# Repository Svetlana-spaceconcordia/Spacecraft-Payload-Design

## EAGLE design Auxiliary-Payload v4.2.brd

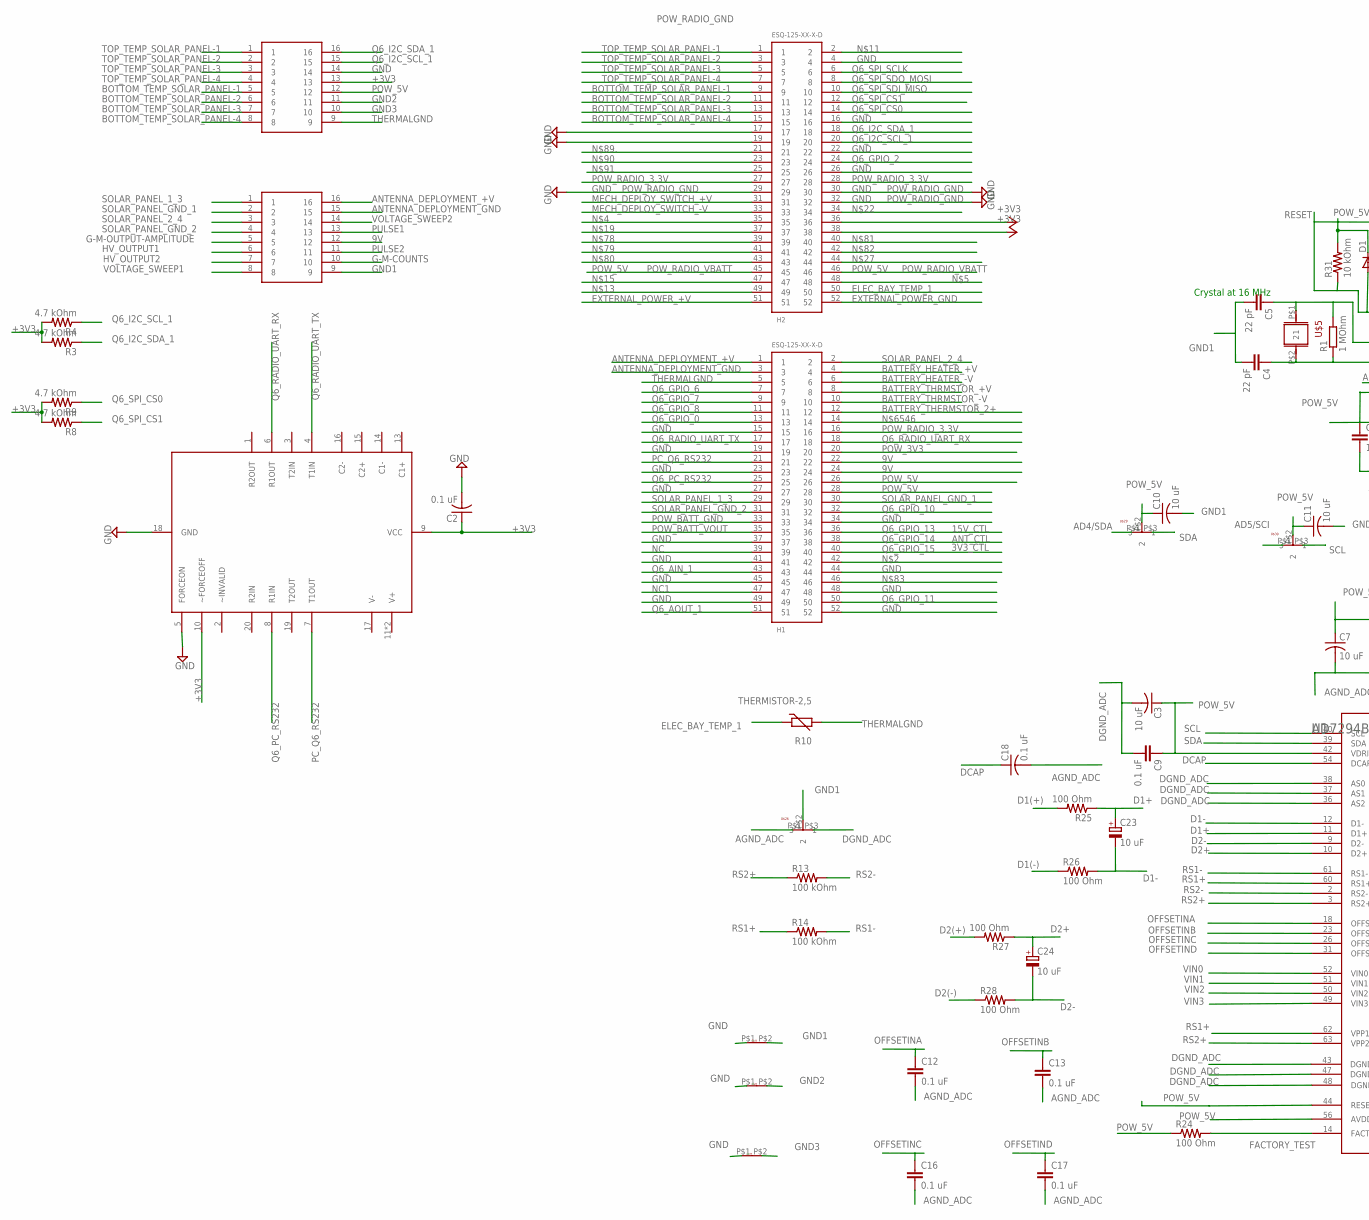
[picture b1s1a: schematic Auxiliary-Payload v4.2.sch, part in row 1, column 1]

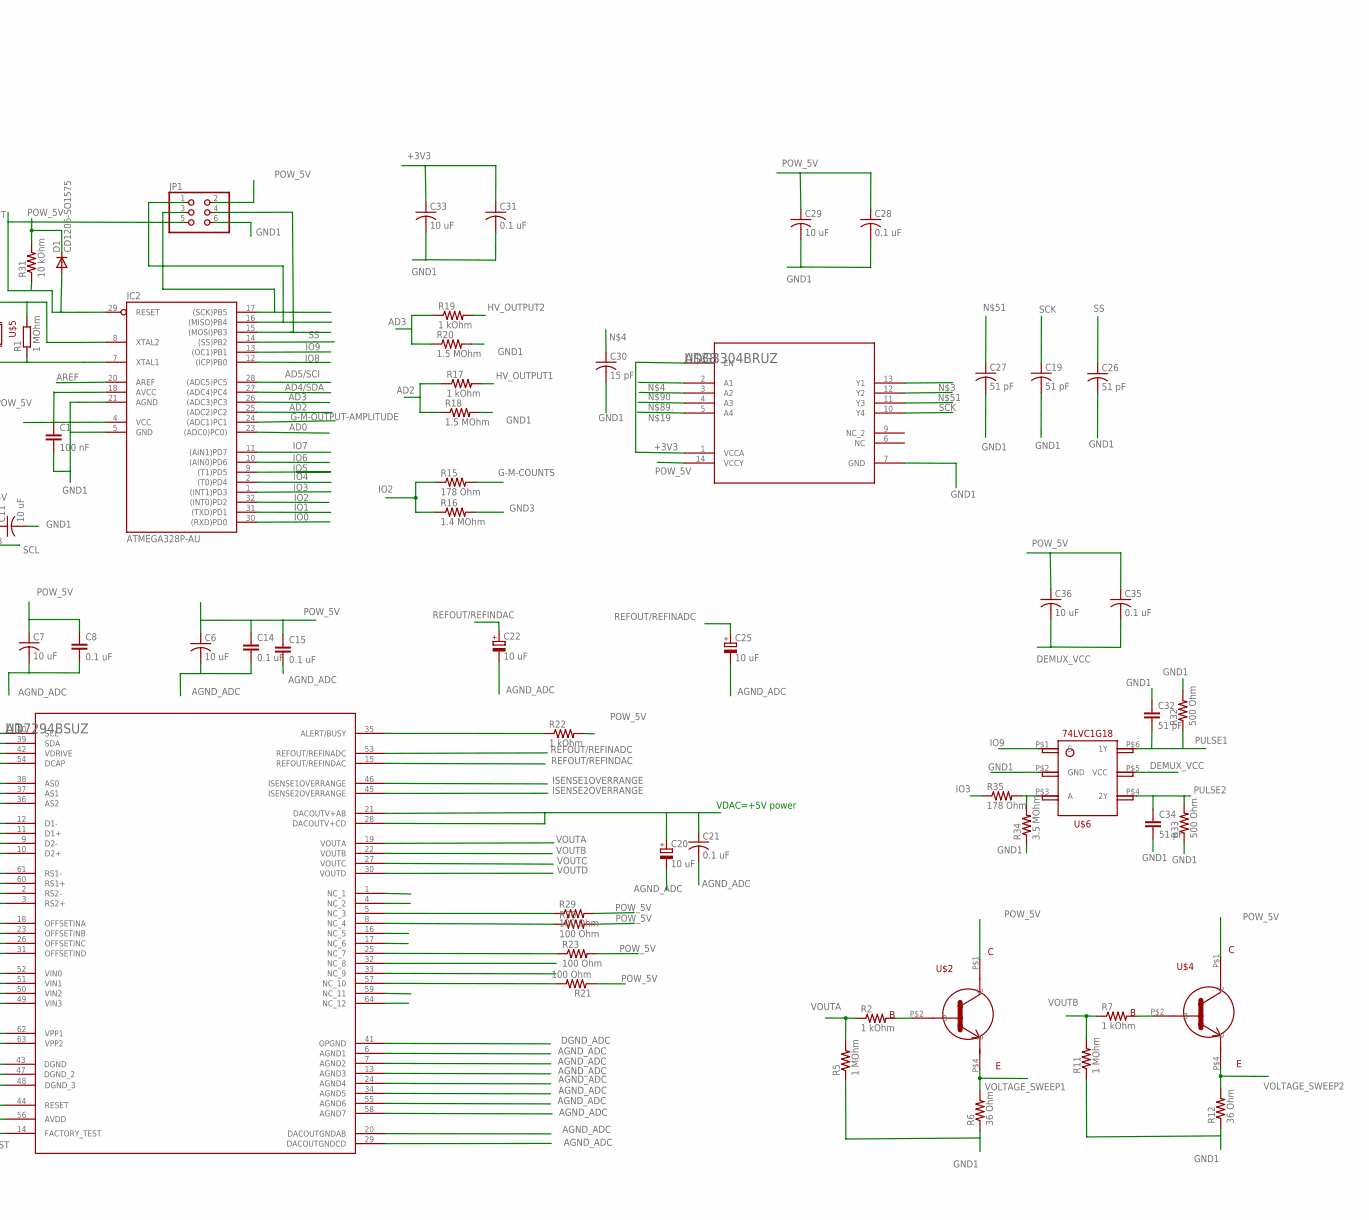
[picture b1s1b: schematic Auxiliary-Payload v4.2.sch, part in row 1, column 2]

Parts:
C1: 100 nF; C0603-ROUND
C2: 0.1 uF; C2012
C3, C6, C7, C10, C11, C29, C33, C36: 10 uF; C1210
C4, C5: 22 pF; C0603-ROUND
C8, C9, C12, C13, C14, C15, C16, C17, C18, C21, C28, C31, C35: 0.1 uF; C0603
C19, C26, C27, C32, C34: 51 pF; C0603
C20, C22, C23, C24, C25: 10 uF; C/6032-28W
C30: 15 pF; C0603
D1: CD1206-SO1575; MINIMELF
H1, H2: ESQ-125-XX-X-D
IC2: ATMEGA328P-AU; TQFP32-08
JP1: PINHD-2X3; 2X03
R1: 1 MOhm; R0603-ROUND
R2, R7: 1 kOhm; R1206
R3, R4, R8, R9: 4.7 kOhm; R2012
R5, R11: 1 MOhm; R2010
R6, R12: 36 Ohm; R2010
R10: THERMISTOR-2,5; RS-2,5
R13, R14: 100 kOhm; R0805
R15: 178 Ohm; R1206
R16: 1.4 MOhm; R1206
R17, R19, R22: 1 kOhm; R0805
R18, R20: 1.5 MOhm; R0805
R21, R23, R24, R25, R26, R27, R28, R29, R30: 100 Ohm; R0603
R31: 10 kOhm; R0603
R32, R33: 500 Ohm; R0805
R34: 3.5 MOhm; R1206
R35: 178 Ohm; R1210
U1: AD7294BSUZ; SU_64_1
U$1, U$3: M80-866XXXX
U$2, U$4: FZT651-NPN-TRANSISTOR; SOT223-PZT3904
U$5: CSM-7X-DU-CRYSTAL-ARDUINO; CSM-7X-DU-CRYSTAL
U$6: 74LVC1G18-SOT363; SOT-363
U$8: MAX3233; SO20L
U$26, U$29, U$30: CONNECTOR-3; CONNECTOR-3T
U$33, U$34, U$36: CONNECTOR-SHORT; CONNECTOR-T
U$38: ADG3304BRUZ; RU_14

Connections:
9V: H1.22, H1.24, U$1.12
+3V3: C2.1, C31.1, C33.1, H2.36, H2.38, R3.2, R4.2, R8.2, R9.2, U$3.13, U$8.9 (VCC), U$8.10 (~FORCEOFF), U$38.1 (VCCA), U$38.8 (EN)
A: R34.2, R35.2, U$6.P$3 (A)
AD0: IC2.23 ((ADC0)PC0))
AD2: IC2.25 ((ADC2)PC2), R17.1, R18.1
AD3: IC2.26 ((ADC3)PC3), R19.1, R20.1
AD4/SDA: IC2.27 ((ADC4)PC4), U$29.P$1 (1)
AD5/SCI: IC2.28 ((ADC5)PC5), U$30.P$1 (1)
AGND_ADC: C3.2, C6.2, C7.2, C8.2, C9.2, C12.2, C13.2, C14.2, C15.2, C16.2, C17.2, C18.2, C20.-, C21.2, C22.-, C25.-, U1.6 (AGND1), U1.7 (AGND2), U1.13 (AGND3), U1.20 (DACOUTGNDAB), U1.24 (AGND4), U1.29 (DACOUTGNDCD), U1.34 (AGND5), U1.55 (AGND6), U1.58 (AGND7), U$26.P$1 (1)
ALERT/BUSY: R22.1, U1.35 (ALERT/BUSY)
ANTENNA_DEPLOYMENT_+V: H1.1, U$1.16
ANTENNA_DEPLOYMENT_GND: H1.3, U$1.15
AREF: IC2.20 (AREF)
BATTERY_HEATER_+V: H1.4
BATTERY_HEATER_-V: H1.6
BATTERY_THERMSTOR_2+: H1.12
BATTERY_THRMSTOR_+V: H1.8
BATTERY_THRMSTOR_-V: H1.10
BOTTOM_TEMP_SOLAR_PANEL-1: H2.9, U$3.5
BOTTOM_TEMP_SOLAR_PANEL-2: H2.11, U$3.6
BOTTOM_TEMP_SOLAR_PANEL-3: H2.13, U$3.7
BOTTOM_TEMP_SOLAR_PANEL-4: H2.15, U$3.8
D1(+): R25.2
D1(-): R26.1
D1+: C23.+, R25.1, U1.11 (D1+)
D1-: C23.-, R26.2, U1.12 (D1-)
D2(+): R27.2
D2(-): R28.1
D2+: C24.+, R27.1, U1.10 (D2+)
D2-: C24.-, R28.2, U1.9 (D2-)
DCAP: C18.1, U1.54 (DCAP)
DEMUX_VCC: C35.2, C36.2, U$6.P$5 (VCC)
DGND_ADC: U1.36 (AS2), U1.37 (AS1), U1.38 (AS0), U1.41 (OPGND), U1.43 (DGND), U1.47 (DGND_2), U1.48 (DGND_3), U$26.P$3 (3)
ELEC_BAY_TEMP_1: H2.50, R10.1
EXTERNAL_POWER_+V: H2.51
EXTERNAL_POWER_GND: H2.52
FACTORY_TEST: R24.2, U1.14 (FACTORY_TEST)
G-M-COUNTS: R15.2, U$1.10
G-M-OUTPUT-AMPLITUDE: IC2.24 ((ADC1)PC1), U$1.5
GND: H1.15, H1.19, H1.23, H1.27, H1.34, H1.37, H1.41, H1.44, H1.45, H1.48, H1.49, H1.52, H2.4, H2.16, H2.17, H2.19, H2.22, H2.26, H2.29, H2.30, H2.32, U$3.14, U$33.P$1 (IN), U$34.P$1 (IN), U$36.P$1 (IN)
GND1: C1.2, C2.2, C4.2, C5.2, C10.2, C11.2, C19.2, C26.2, C27.2, C28.2, C29.2, C30.2, C31.2, C32.1, C33.2, C34.2, IC2.5 (GND), IC2.21 (AGND), JP1.6, R5.1, R6.1, R11.1, R12.1, R18.2, R20.2, R32.2, R33.1, R34.1, U$1.9, U$6.P$2 (GND), U$8.5 (FORCEON), U$8.18 (GND), U$26.P$2 (2), U$33.P$2 (OUT), U$38.7 (GND)
GND2: U$3.11, U$34.P$2 (OUT)
GND3: R16.2, U$3.10, U$36.P$2 (OUT)
HV_OUTPUT1: R17.2, U$1.6
HV_OUTPUT2: R19.2, U$1.7
IO0: IC2.30 ((RXD)PD0)
IO1: IC2.31 ((TXD)PD1)
IO2: IC2.32 ((INT0)PD2), R15.1, R16.1
IO3: IC2.1 ((INT1)PD3), R35.1
IO4: IC2.2 ((T0)PD4)
IO5: IC2.9 ((T1)PD5)
IO6: IC2.10 ((AIN0)PD6)
IO7: IC2.11 ((AIN1)PD7)
IO8: IC2.12 ((ICP)PB0)
IO9: IC2.13 ((OC1)PB1), U$6.P$1 (S)
ISENSE1OVERRANGE: U1.46 (ISENSE1OVERRANGE)
ISENSE2OVERRANGE: U1.45 (ISENSE2OVERRANGE)
MECH_DEPLOY_SWITCH_+V: H2.31
MECH_DEPLOY_SWITCH_-V: H2.33
unnamed: IC2.16 ((MISO)PB4), JP1.1, U$38.13 (Y1)
unnamed: C30.1, H2.35, U$38.2 (A1)
unnamed: H2.37, U$38.5 (A4)
unnamed: R7.2, U$4.P$2 (B)
unnamed: C4.1, IC2.7 (XTAL1), R1.1, U$5.P$2 (2)
unnamed: C5.1, IC2.8 (XTAL2), R1.2, U$5.P$1 (1)
unnamed: C27.1, IC2.15 ((MOSI)PB3), JP1.4, U$38.12 (Y2)
unnamed: R2.2, U$2.P$2 (B)
unnamed: H2.21, U$38.4 (A3)
unnamed: H2.23, U$38.3 (A2)
NC: H1.39
NC1: H1.47
NC_1: U1.1 (NC_1)
NC_2: U1.4 (NC_2)
NC_3: R29.1, U1.5 (NC_3)
NC_4: R30.1, U1.8 (NC_4)
NC_5: U1.16 (NC_5)
NC_6: U1.17 (NC_6)
NC_7: R23.1, U1.25 (NC_7)
NC_8: U1.32 (NC_8)
NC_9: U1.33 (NC_9)
NC_10: R21.2, U1.57 (NC_10)
NC_11: U1.59 (NC_11)
NC_12: U1.64 (NC_12)
OFFSETINA: C12.1, U1.18 (OFFSETINA)
OFFSETINB: C13.1, U1.23 (OFFSETINB)
OFFSETINC: C16.1, U1.26 (OFFSETINC)
OFFSETIND: C17.1, U1.31 (OFFSETIND)
PC_Q6_RS232: H1.21, U$8.7 (T1OUT)
POW_3V3: H1.20
POW_5V: C1.1, C3.1, C6.1, C7.1, C8.1, C9.1, C10.1, C11.1, C14.1, C15.1, C20.+, C21.1, C28.1, C29.1, C35.1, C36.1, D1.C, H1.26, H1.28, H2.45, H2.46, IC2.4 (VCC), IC2.18 (AVCC), JP1.2, R21.1, R22.2, R23.2, R24.1, R29.2, R30.2, R31.2, U1.21 (DACOUTV+AB), U1.28 (DACOUTV+CD), U1.42 (VDRIVE), U1.44 (RESET), U1.56 (AVDD), U$2.P$1 (C), U$3.12, U$4.P$1 (C), U$29.P$2 (2), U$30.P$2 (2), U$38.14 (VCCY)
POW_BATT_GND: H1.33
POW_BATT_VOUT: H1.35
POW_RADIO_3.3V: H1.16, H2.27, H2.28
PULSE1: C32.2, R32.1, U$1.13, U$6.P$6 (1Y)
PULSE2: C34.1, R33.2, U$1.11, U$6.P$4 (2Y)
Q6_AIN_1: H1.43
Q6_AOUT_1: H1.51
Q6_GPIO_0: H1.13
Q6_GPIO_2: H2.24
Q6_GPIO_6: H1.7
Q6_GPIO_7: H1.9
Q6_GPIO_8: H1.11
Q6_GPIO_10: H1.32
Q6_GPIO_11: H1.50
Q6_GPIO_13: H1.36
Q6_GPIO_14: H1.38
Q6_GPIO_15: H1.40
Q6_I2C_SCL_1: H2.20, R4.1, U$3.15
Q6_I2C_SDA_1: H2.18, R3.1, U$3.16
Q6_PC_RS232: H1.25, U$8.8 (R1IN)
Q6_RADIO_UART_RX: H1.18, U$8.6 (R1OUT)
Q6_RADIO_UART_TX: H1.17, U$8.4 (T1IN)
Q6_SPI_CS0: H2.14, R9.1
Q6_SPI_CS1: H2.12, R8.1
Q6_SPI_SCLK: H2.6
Q6_SPI_SDI_MISO: H2.10
Q6_SPI_SDO_MOSI: H2.8
REFOUT/REFINADC: C25.+, U1.53 (REFOUT/REFINADC)
REFOUT/REFINDAC: C22.+, U1.15 (REFOUT/REFINDAC)
RESET: D1.A, IC2.29 (RESET), JP1.5, R31.1
RS1+: R14.1, U1.60 (RS1+), U1.62 (VPP1)
RS1-: R14.2, U1.61 (RS1-)
RS2+: R13.1, U1.3 (RS2+), U1.63 (VPP2)
RS2-: R13.2, U1.2 (RS2-)
SCK: C19.1, IC2.17 ((SCK)PB5), JP1.3, U$38.11 (Y3)
SCL: U1.40 (SCL), U$30.P$3 (3)
SDA: U1.39 (SDA), U$29.P$3 (3)
SOLAR_PANEL_1_3: H1.29, U$1.1
SOLAR_PANEL_2_4: H1.2, U$1.3
SOLAR_PANEL_GND_1: H1.30, U$1.2
SOLAR_PANEL_GND_2: H1.31, U$1.4
SS: C26.1, IC2.14 ((SS)PB2), U$38.10 (Y4)
THERMALGND: H1.5, R10.2, U$3.9
TOP_TEMP_SOLAR_PANEL-1: H2.1, U$3.1
TOP_TEMP_SOLAR_PANEL-2: H2.3, U$3.2
TOP_TEMP_SOLAR_PANEL-3: H2.5, U$3.3
TOP_TEMP_SOLAR_PANEL-4: H2.7, U$3.4
VIN0: U1.52 (VIN0)
VIN1: U1.51 (VIN1)
VIN2: U1.50 (VIN2)
VIN3: U1.49 (VIN3)
VOLTAGE_SWEEP1: R6.2, U$1.8, U$2.P$4 (E)
VOLTAGE_SWEEP2: R12.2, U$1.14, U$4.P$4 (E)
VOUTA: R2.1, R5.2, U1.19 (VOUTA)
VOUTB: R7.1, R11.2, U1.22 (VOUTB)
VOUTC: U1.27 (VOUTC)
VOUTD: U1.30 (VOUTD)

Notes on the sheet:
POW_RADIO_GND
15V_CTL
ANT_CTL
SOLAR_PANEL_2_4
3V3_CTL
POW_RADIO_VBATT
Crystal at 16 MHz
VDAC=+5V power

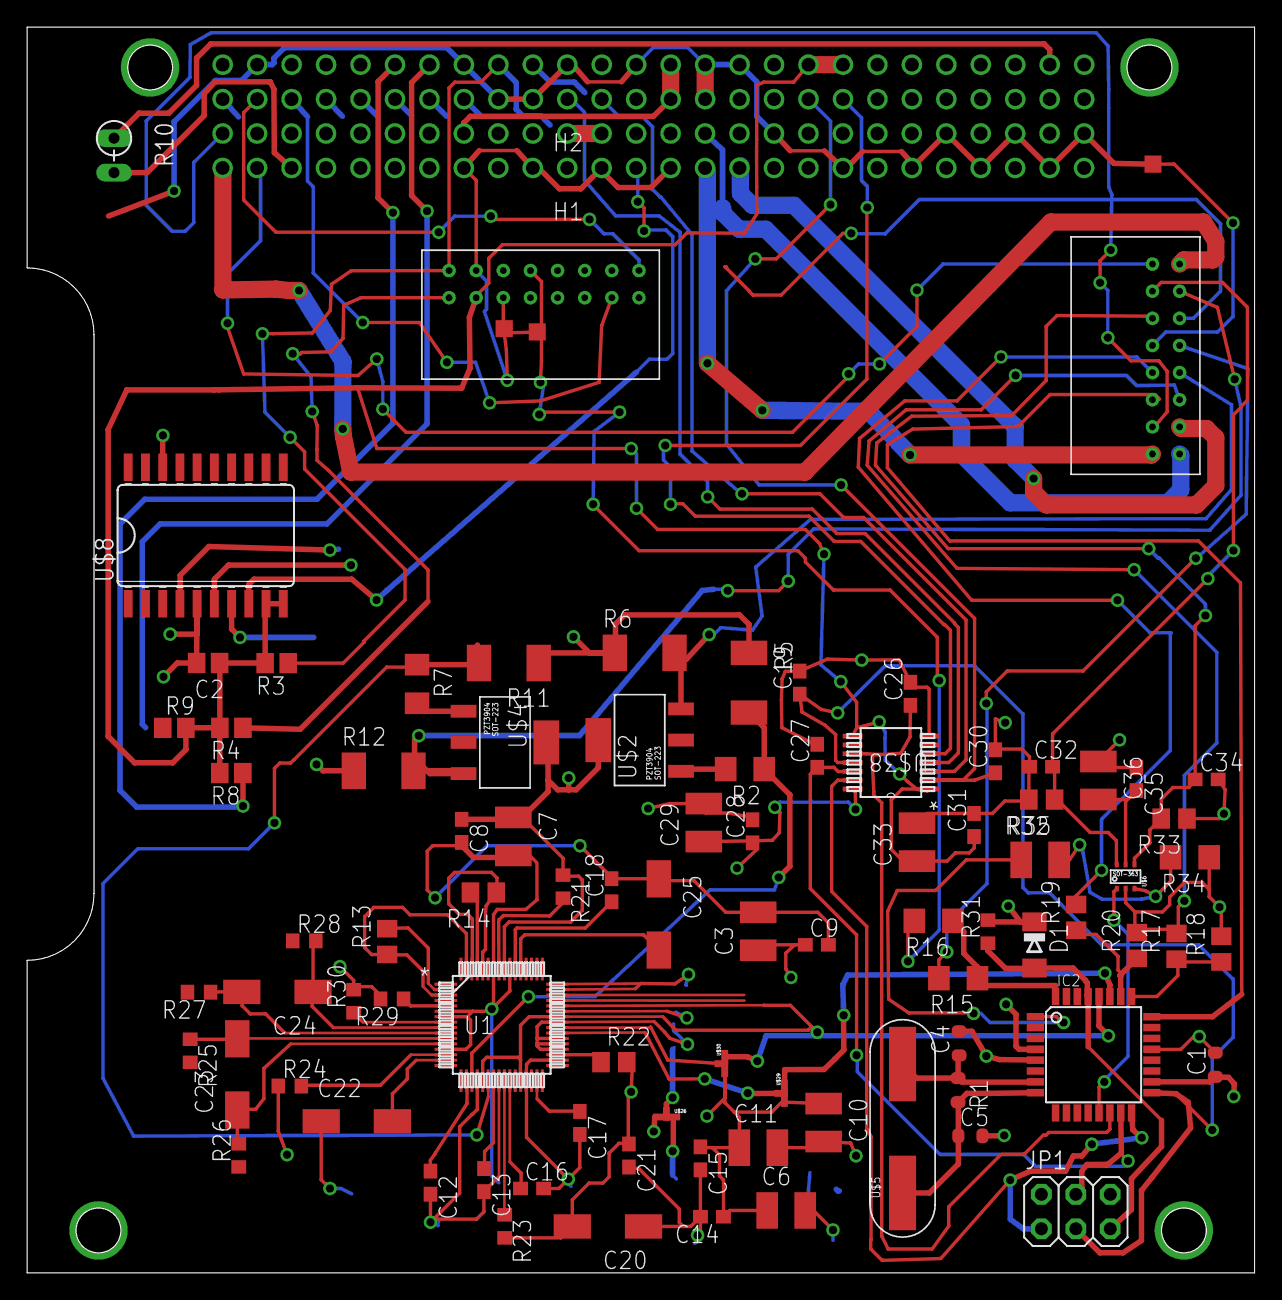
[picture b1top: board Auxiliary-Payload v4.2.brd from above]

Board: 4 copper layers, 90.5 x 91.8 mm, 91 parts (0 on the bottom side), 89 nets.

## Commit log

2015-12-18 Auxiliary-Payload v4.2.brd
2015-12-18 Auxiliary-Payload v4.2.sch
